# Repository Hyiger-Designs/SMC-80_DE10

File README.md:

A daughter card for the [DE10-Lite Board](http://www.terasic.com.tw/cgi-bin/page/archive.pl?Language=English&No=1021) supports: SPI, I2C, Serial, SRAM, and 40-pin IDE. Can be used with Grant Searle's multicomp project.

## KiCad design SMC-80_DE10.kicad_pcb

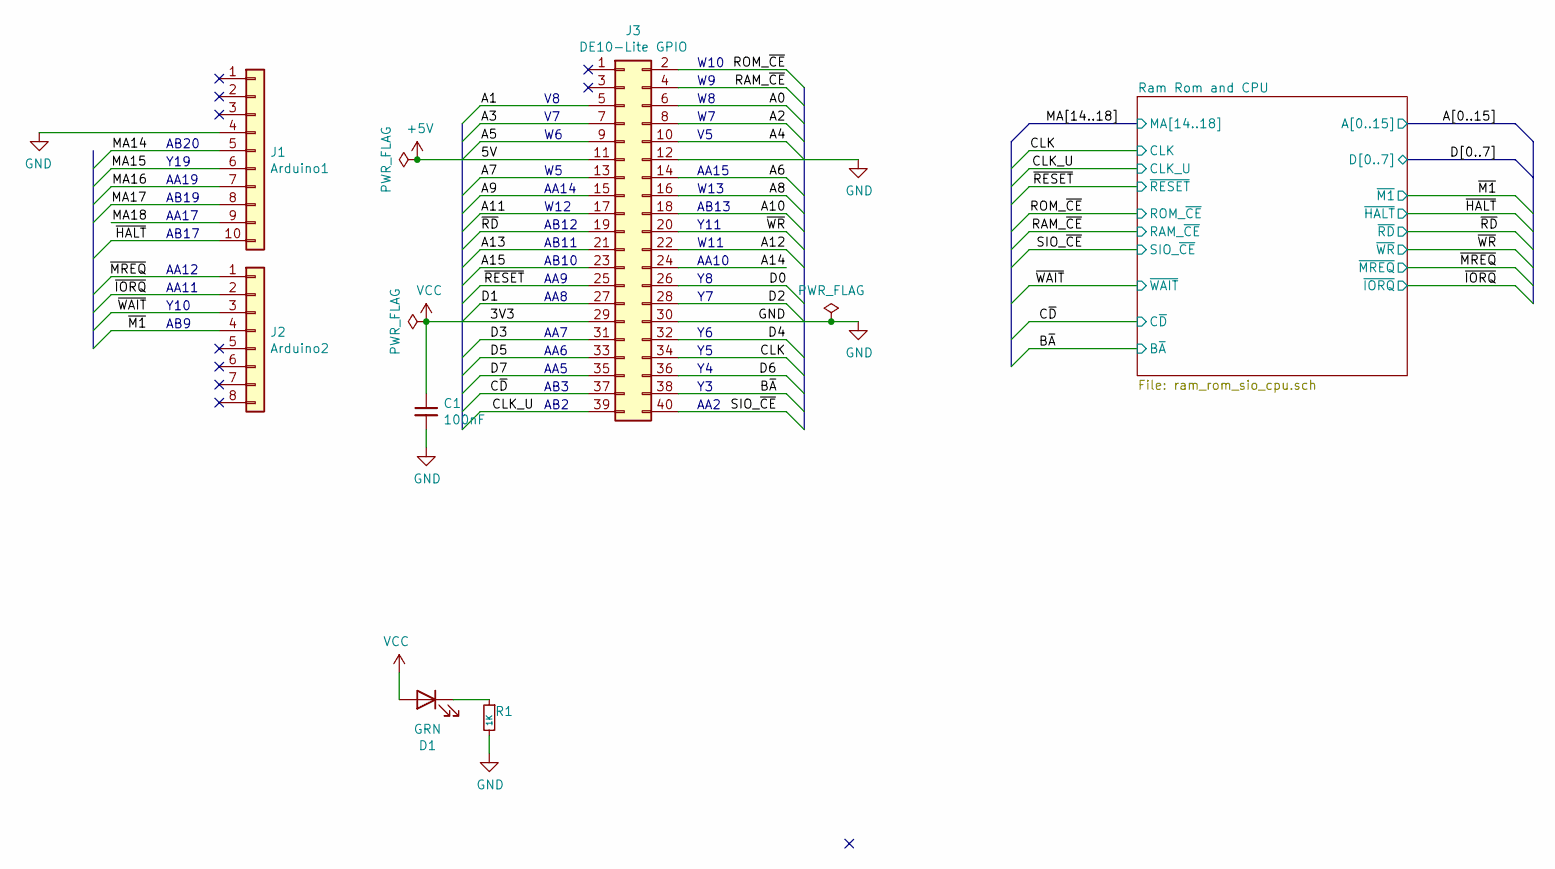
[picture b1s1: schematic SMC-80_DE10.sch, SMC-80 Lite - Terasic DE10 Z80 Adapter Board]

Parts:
C1: 100nF; C_0603_1608Metric_Pad1.05x0.95mm_HandSolder
D1: GRN; LED_0603_1608Metric_Pad1.05x0.95mm_HandSolder
J1: Arduino1; PinHeader_1x10_P2.54mm_Vertical
J2: Arduino2; PinHeader_1x08_P2.54mm_Vertical
J3: DE10-Lite GPIO; PinSocket_2x20_P2.54mm_Vertical
R1: 1K; R_0603_1608Metric_Pad1.05x0.95mm_HandSolder

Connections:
+5V: J3.11
/A0: J3.6; also elsewhere on the board
/A1: J3.5; also elsewhere on the board
/A2: J3.8; also elsewhere on the board
/A3: J3.7; also elsewhere on the board
/A4: J3.10; also elsewhere on the board
/A5: J3.9; also elsewhere on the board
/A6: J3.14; also elsewhere on the board
/A7: J3.13; also elsewhere on the board
/A8: J3.16; also elsewhere on the board
/A9: J3.15; also elsewhere on the board
/A10: J3.18; also elsewhere on the board
/A11: J3.17; also elsewhere on the board
/A12: J3.22; also elsewhere on the board
/A13: J3.21; also elsewhere on the board
/A14: J3.24; also elsewhere on the board
/A15: J3.23; also elsewhere on the board
/B~A: J3.38; also elsewhere on the board
/CLK: J3.34; also elsewhere on the board
/CLK_U: J3.39; also elsewhere on the board
/C~D: J3.37; also elsewhere on the board
/D0: J3.26; also elsewhere on the board
/D1: J3.27; also elsewhere on the board
/D2: J3.28; also elsewhere on the board
/D3: J3.31; also elsewhere on the board
/D4: J3.32; also elsewhere on the board
/D5: J3.33; also elsewhere on the board
/D6: J3.36; also elsewhere on the board
/D7: J3.35; also elsewhere on the board
/MA14: J1.5; also elsewhere on the board
/MA15: J1.6; also elsewhere on the board
/MA16: J1.7; also elsewhere on the board
/MA17: J1.8; also elsewhere on the board
/MA18: J1.9; also elsewhere on the board
/RAM_~CE: J3.4; also elsewhere on the board
/ROM_~CE: J3.2; also elsewhere on the board
/SIO_~CE: J3.40; also elsewhere on the board
/~HALT: J1.10; also elsewhere on the board
/~IORQ: J2.2; also elsewhere on the board
/~M1: J2.4; also elsewhere on the board
/~MREQ: J2.1; also elsewhere on the board
/~RD: J3.19; also elsewhere on the board
/~RESET: J3.25; also elsewhere on the board
/~WAIT: J2.3; also elsewhere on the board
/~WR: J3.20; also elsewhere on the board
GND: C1.2, J1.4, J3.12, J3.30, R1.2; also elsewhere on the board
unnamed: D1.1 (K), R1.1
VCC: C1.1, D1.2 (A), J3.29; also elsewhere on the board

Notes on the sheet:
AB9
AA19
Y19
AB20
AB2
AB12
AB11
AB10
AA9
AA8
W11
AA10
AA7
AA6
W12
AA2
Y11
AB13
W13
AA15
W10
AA14
AA12
AA11
Y10
AB19
AA17
AB17
AA5
AB3

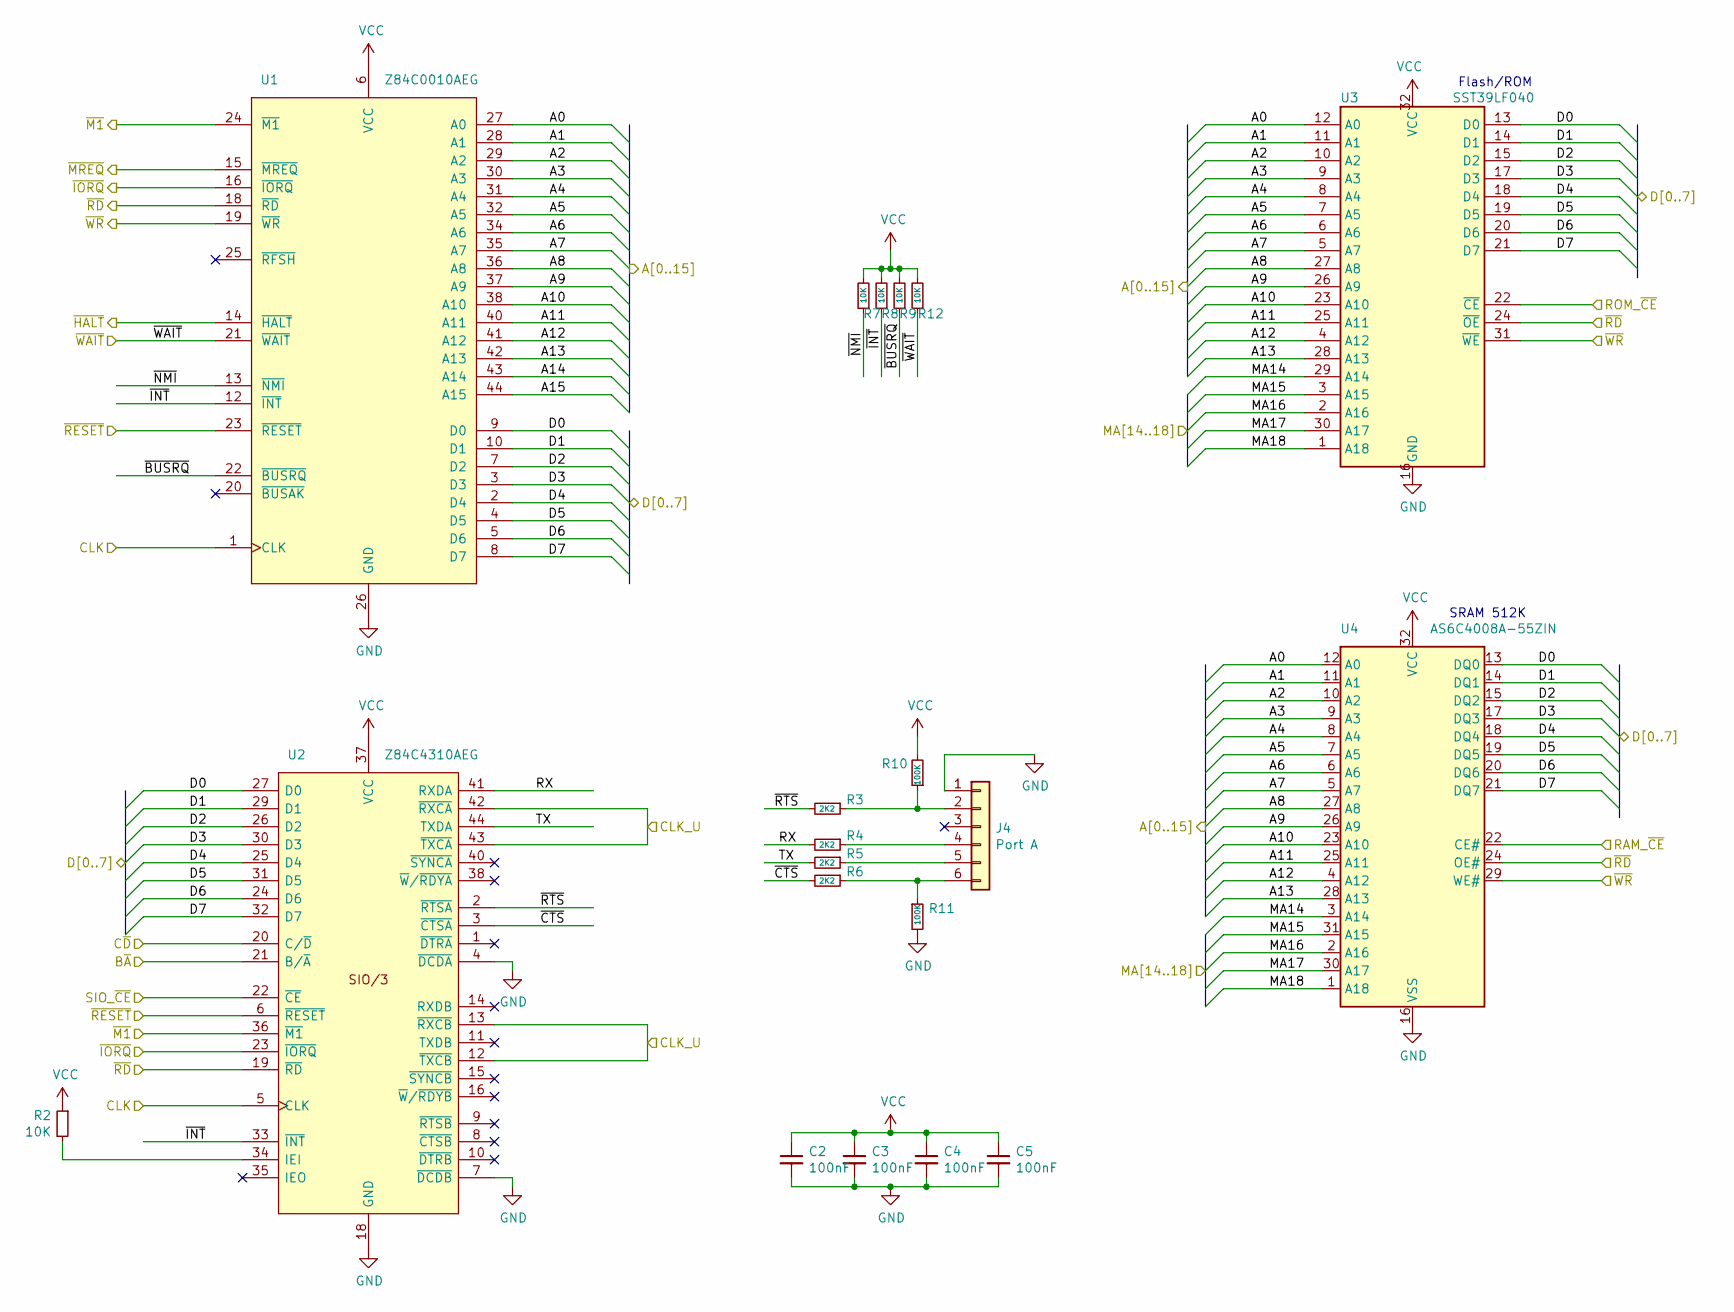
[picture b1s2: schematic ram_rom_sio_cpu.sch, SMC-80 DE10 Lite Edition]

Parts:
C2, C3, C4, C5: 100nF; C_0603_1608Metric_Pad1.05x0.95mm_HandSolder
J4: Port A; PinHeader_1x06_P2.54mm_Vertical
R2, R7, R8, R9, R12: 10K; R_0603_1608Metric_Pad1.05x0.95mm_HandSolder
R3, R4, R5, R6: 2K2; R_0603_1608Metric_Pad1.05x0.95mm_HandSolder
R10, R11: 100K; R_0603_1608Metric_Pad1.05x0.95mm_HandSolder
U1: Z84C0010AEG; LQFP-44_10x10mm_P0.8mm; Manufacturer_Part_Number Z84C0010AEG
U2: Z84C4310AEG; LQFP-44_10x10mm_P0.8mm; Manufacturer_Part_Number Z84C4310AEG
U3: SST39LF040; PLCC-32_11.4x14.0mm_P1.27mm-Socket; Manufacturer_Part_Number SST39LF040-55-4C-NHE
U4: AS6C4008A-55ZIN; TSOP-II-32_21.0x10.2mm_P1.27mm; Manufacturer_Part_Number AS6C4008A-55ZIN

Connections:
/A0: U1.27 (A0), U3.12 (A0), U4.12 (A0); also elsewhere on the board
/A1: U1.28 (A1), U3.11 (A1), U4.11 (A1); also elsewhere on the board
/A2: U1.29 (A2), U3.10 (A2), U4.10 (A2); also elsewhere on the board
/A3: U1.30 (A3), U3.9 (A3), U4.9 (A3); also elsewhere on the board
/A4: U1.31 (A4), U3.8 (A4), U4.8 (A4); also elsewhere on the board
/A5: U1.32 (A5), U3.7 (A5), U4.7 (A5); also elsewhere on the board
/A6: U1.34 (A6), U3.6 (A6), U4.6 (A6); also elsewhere on the board
/A7: U1.35 (A7), U3.5 (A7), U4.5 (A7); also elsewhere on the board
/A8: U1.36 (A8), U3.27 (A8), U4.27 (A8); also elsewhere on the board
/A9: U1.37 (A9), U3.26 (A9), U4.26 (A9); also elsewhere on the board
/A10: U1.38 (A10), U3.23 (A10), U4.23 (A10); also elsewhere on the board
/A11: U1.40 (A11), U3.25 (A11), U4.25 (A11); also elsewhere on the board
/A12: U1.41 (A12), U3.4 (A12), U4.4 (A12); also elsewhere on the board
/A13: U1.42 (A13), U3.28 (A13), U4.28 (A13); also elsewhere on the board
/A14: U1.43 (A14); also elsewhere on the board
/A15: U1.44 (A15); also elsewhere on the board
/B~A: U2.21 (B/~A); also elsewhere on the board
/CLK: U1.1 (CLK), U2.5 (CLK); also elsewhere on the board
/CLK_U: U2.12 (~TXCB), U2.13 (~RXCB), U2.42 (~RXCA), U2.43 (~TXCA); also elsewhere on the board
/C~D: U2.20 (C/~D); also elsewhere on the board
/D0: U1.9 (D0), U2.27 (D0), U3.13 (D0), U4.13 (DQ0); also elsewhere on the board
/D1: U1.10 (D1), U2.29 (D1), U3.14 (D1), U4.14 (DQ1); also elsewhere on the board
/D2: U1.7 (D2), U2.26 (D2), U3.15 (D2), U4.15 (DQ2); also elsewhere on the board
/D3: U1.3 (D3), U2.30 (D3), U3.17 (D3), U4.17 (DQ3); also elsewhere on the board
/D4: U1.2 (D4), U2.25 (D4), U3.18 (D4), U4.18 (DQ4); also elsewhere on the board
/D5: U1.4 (D5), U2.31 (D5), U3.19 (D5), U4.19 (DQ5); also elsewhere on the board
/D6: U1.5 (D6), U2.24 (D6), U3.20 (D6), U4.20 (DQ6); also elsewhere on the board
/D7: U1.8 (D7), U2.32 (D7), U3.21 (D7), U4.21 (DQ7); also elsewhere on the board
/MA14: U3.29 (A14), U4.3 (A14); also elsewhere on the board
/MA15: U3.3 (A15), U4.31 (A15); also elsewhere on the board
/MA16: U3.2 (A16), U4.2 (A16); also elsewhere on the board
/MA17: U3.30 (A17), U4.30 (A17); also elsewhere on the board
/MA18: U3.1 (A18), U4.1 (A18); also elsewhere on the board
/RAM_~CE: U4.22 (CE#); also elsewhere on the board
/ROM_~CE: U3.22 (~CE); also elsewhere on the board
/Ram Rom and CPU/RX: R4.2, U2.41 (RXDA)
/Ram Rom and CPU/TX: R5.2, U2.44 (TXDA)
/Ram Rom and CPU/~BUSRQ: R9.1, U1.22 (~BUSRQ)
/Ram Rom and CPU/~CTS: R6.2, U2.3 (~CTSA)
/Ram Rom and CPU/~INT: R8.1, U1.12 (~INT), U2.33 (~INT)
/Ram Rom and CPU/~NMI: R7.1, U1.13 (~NMI)
/Ram Rom and CPU/~RTS: R3.2, U2.2 (~RTSA)
/SIO_~CE: U2.22 (~CE); also elsewhere on the board
/~HALT: U1.14 (~HALT); also elsewhere on the board
/~IORQ: U1.16 (~IORQ), U2.23 (~IORQ); also elsewhere on the board
/~M1: U1.24 (~M1), U2.36 (~M1); also elsewhere on the board
/~MREQ: U1.15 (~MREQ); also elsewhere on the board
/~RD: U1.18 (~RD), U2.19 (~RD), U3.24 (~OE), U4.24 (OE#); also elsewhere on the board
/~RESET: U1.23 (~RESET), U2.6 (~RESET); also elsewhere on the board
/~WAIT: R12.1, U1.21 (~WAIT); also elsewhere on the board
/~WR: U1.19 (~WR), U3.31 (~WE), U4.29 (WE#); also elsewhere on the board
GND: C2.2, C3.2, C4.2, C5.2, J4.1, R11.2, U1.26 (GND), U2.4 (~DCDA), U2.7 (~DCDB), U2.18 (GND), U3.16 (GND), U4.16 (VSS); also elsewhere on the board
unnamed: J4.2, R3.1, R10.1
unnamed: J4.4, R4.1
unnamed: J4.5, R5.1
unnamed: J4.6, R6.1, R11.1
unnamed: R2.2, U2.34 (IEI)
VCC: C2.1, C3.1, C4.1, C5.1, R2.1, R7.2, R8.2, R9.2, R10.2, R12.2, U1.6 (VCC), U2.37 (VCC), U3.32 (VCC), U4.32 (VCC); also elsewhere on the board

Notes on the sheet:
Flash/ROM
SRAM 512K

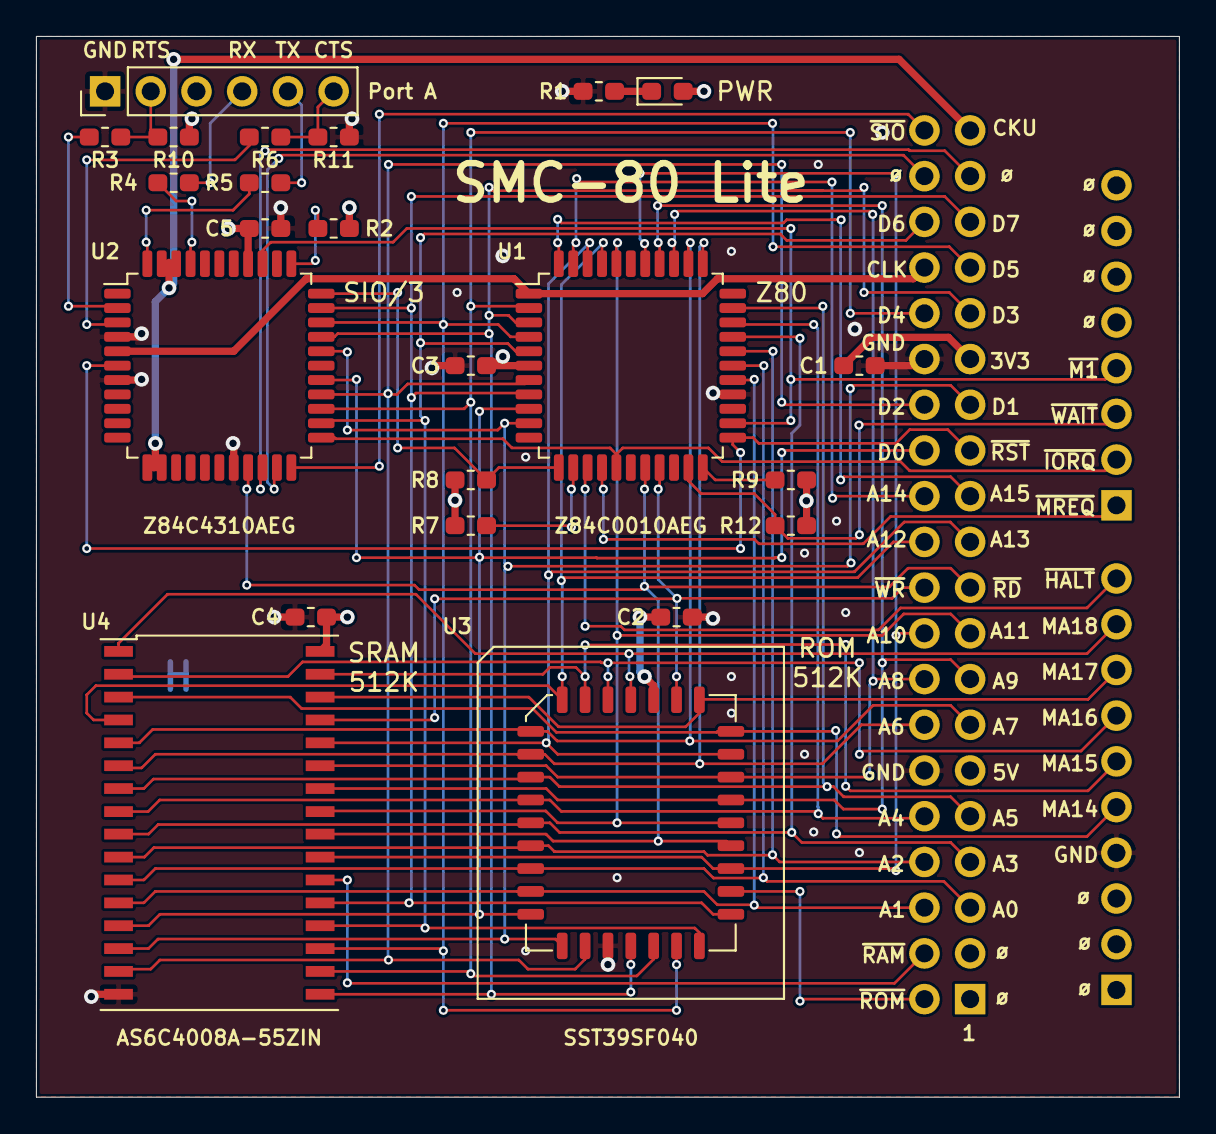
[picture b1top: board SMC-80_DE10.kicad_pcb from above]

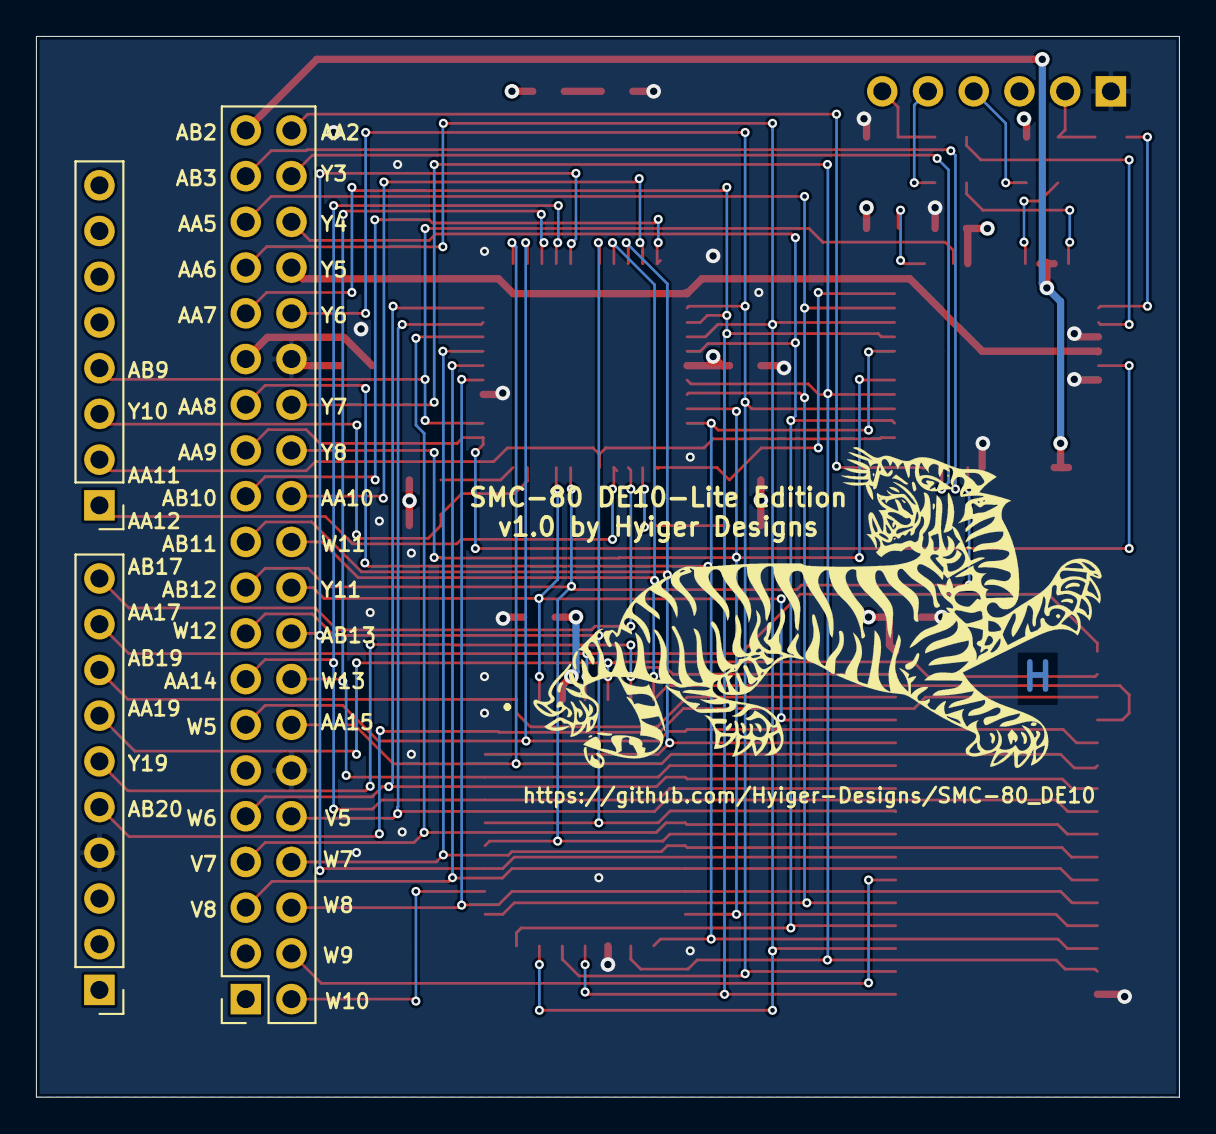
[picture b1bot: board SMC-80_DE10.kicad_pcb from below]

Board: 4 copper layers, 63.5 x 58.9 mm, 26 parts (3 on the bottom side), 59 nets.

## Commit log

2020-04-22 Initial version
2020-04-22 Renamed to SMC-80 DE10, new layout
2020-04-22 added kicad specific gitignore
2020-04-23 rotated layout
2020-04-23 Routing completed, fixed RAM/ROM paging
2020-04-24 added gnd plane stitching
2020-04-24 enhanced graphic for PLCC socket
2020-04-25 removed ram/rom ce pullups
2020-04-28 added FPGA pin labels
2020-04-28 shifted Arduino pins
2020-04-28 shifted some components
2020-04-29 checkpoint
2020-05-01 final version 1.0
2020-05-01 fixed DRC error
2020-05-01 Fixed up silkscreens
2020-05-02 normalize symbols
2020-05-02 reorganized SIO
2020-05-02 fixed up gnd plane regions
2020-05-03 reorganized schematic, added missing pin label
2020-05-04 added SIO port B clock
2020-05-05 Broke out SIO C/D and B/A pins
2020-05-06 Add bottom silkscreens for FPGA pins
2020-05-06 extra space for z80 pullups
2020-05-07 smoothed traces
2020-05-07 added version and titles to schematic and board
2020-05-07 cleanup tracks and vias
2020-05-27 initial version of MMU code
2020-05-27 gnd plane changes
2020-06-02 test benches and bug fixes
